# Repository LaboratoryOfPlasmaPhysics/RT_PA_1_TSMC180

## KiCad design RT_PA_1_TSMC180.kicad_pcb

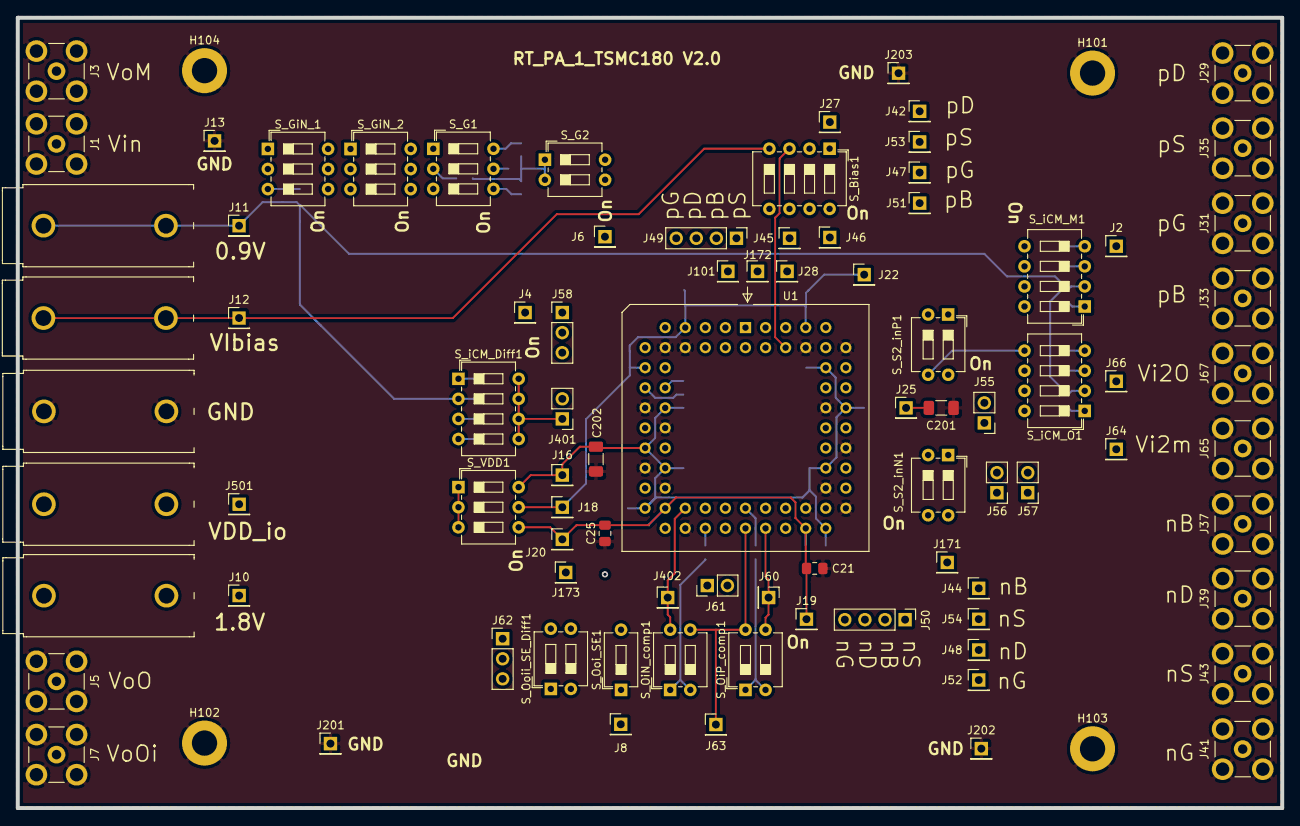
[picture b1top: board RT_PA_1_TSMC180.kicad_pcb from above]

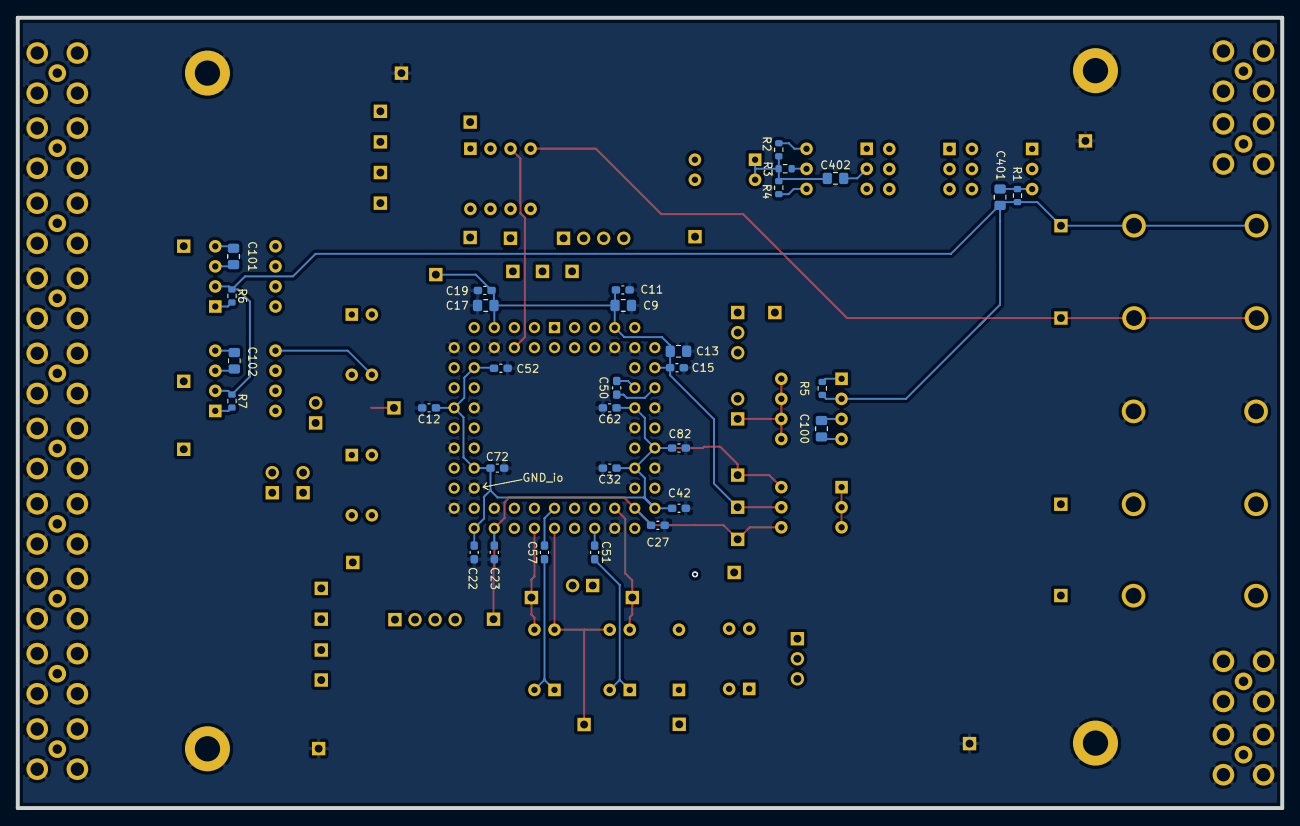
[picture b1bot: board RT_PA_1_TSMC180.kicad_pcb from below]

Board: 4 copper layers, 160.0 x 100.0 mm, 122 parts (31 on the bottom side), 57 nets.

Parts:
C9, C13, C17, C21, C25, C100, C101, C102: 1u; C_0805_2012Metric_Pad1.18x1.45mm_HandSolder
C11, C12, C15, C19, C22, C23, C27, C32, C42, C52, C62, C72, C82: 10n; C_0603_1608Metric_Pad1.08x0.95mm_HandSolder
C50, C51, C57: 1n; C_0603_1608Metric_Pad1.08x0.95mm_HandSolder
C201, C202: 10uF; C_1206_3216Metric_Pad1.33x1.80mm_HandSolder
C401, C402: NC; C_0805_2012Metric_Pad1.18x1.45mm_HandSolder
H101, H102, H103, H104: MountingHole_Pad; MountingHole_3.2mm_M3_ISO7380_Pad
J1, J3, J5, J7, J29, J31, J33, J35, J37, J39, J41, J43, J65, J67: Conn_Coaxial; SMB_Jack_Vertical
J2, J4, J6, J8, J10, J11, J12, J13, J16, J18, J19, J20, J22, J25, J27, J28, J42, J44, J45, J46, J47, J48, J51, J52, J53, J54, J60, J63, J64, J66, J101, J171, J172, J173, J201, J202, J203, J402, J501: Conn_01x01; PinHeader_1x01_P2.54mm_Vertical
J9, J14, J15, J204: Conn_01x01_Female; Banana_test_point_4mm
J49, J50: Conn_01x04; PinHeader_1x04_P2.54mm_Vertical
J55, J56, J57, J61, J401: Conn_01x02; PinHeader_1x02_P2.54mm_Vertical
J58, J62: Conn_01x03; PinHeader_1x03_P2.54mm_Vertical
J_VDD_io501: Conn_01x01_Female; Banana_test_point_4mm
R1: 50; R_0603_1608Metric
R2: 5k; R_0603_1608Metric
R3, R5, R6, R7: 50k; R_0603_1608Metric
R4: 20k; R_0603_1608Metric
S_Bias1: SW_DIP_x04; SW_DIP_SPSTx04_Slide_6.7x11.72mm_W7.62mm_P2.54mm_LowProfile
S_G1: SW_DIP_x03; SW_DIP_SPSTx03_Slide_6.7x9.18mm_W7.62mm_P2.54mm_LowProfile
S_G2: SW_DIP_x02; SW_DIP_SPSTx02_Slide_6.7x6.64mm_W7.62mm_P2.54mm_LowProfile
S_GiN_1, S_GiN_2: SW_DIP_x03; SW_DIP_SPSTx03_Slide_6.7x9.18mm_W7.62mm_P2.54mm_LowProfile
S_OiN_comp1: SW_DIP_x02; SW_DIP_SPSTx02_Slide_6.7x6.64mm_W7.62mm_P2.54mm_LowProfile
S_OiP_comp1: SW_DIP_x02; SW_DIP_SPSTx02_Slide_6.7x6.64mm_W7.62mm_P2.54mm_LowProfile
S_Ooi_SE1: SW_DIP_x01; SW_DIP_SPSTx01_Slide_6.7x4.1mm_W7.62mm_P2.54mm_LowProfile
S_Ooii_SE_Diff1: SW_DIP_x02; SW_DIP_SPSTx02_Slide_6.7x6.64mm_W7.62mm_P2.54mm_LowProfile
S_S2_inN1, S_S2_inP1: SW_DIP_x02; SW_DIP_SPSTx02_Slide_6.7x6.64mm_W7.62mm_P2.54mm_LowProfile
S_VDD1: SW_DIP_x03; SW_DIP_SPSTx03_Slide_6.7x9.18mm_W7.62mm_P2.54mm_LowProfile
S_iCM_Diff1: SW_DIP_x04; SW_DIP_SPSTx04_Slide_6.7x11.72mm_W7.62mm_P2.54mm_LowProfile
S_iCM_M1: SW_DIP_x04; SW_DIP_SPSTx04_Slide_6.7x11.72mm_W7.62mm_P2.54mm_LowProfile
S_iCM_O1: SW_DIP_x04; SW_DIP_SPSTx04_Slide_6.7x11.72mm_W7.62mm_P2.54mm_LowProfile
U1: PART1p68; PLCC-68_THT-Socket

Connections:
/0V9_g: C401.2, J11.1, J14.1, R1.2, R5.2, R6.2, R7.2, S_iCM_Diff1.2, S_iCM_M1.2, S_iCM_O1.2
/1V8_g: J9.1, J10.1, S_VDD1.1, S_VDD1.2, S_VDD1.3
/TCc1: C57.2, J61.2, U1.36
/TCc2: C51.2, J61.1, U1.31
/T_Cc: C50.2, J58.3, U1.14
/VDD_M: C9.1, C11.1, C13.1, C15.1, C17.1, C19.1, J18.1, J22.1, S_VDD1.5, U1.7, U1.12, U1.63
/VDD_O: C21.1, C23.1, C25.1, C27.1, J19.1, J20.1, S_VDD1.4, U1.28, U1.41
/VDD_diff: C12.1, C22.1, C32.1, C42.1, C52.1, C62.1, C72.1, C82.1, C201.1, C202.1, J16.1, J25.1, S_VDD1.6, U1.17, U1.20, U1.23, U1.26, U1.43, U1.49, U1.54, U1.59
/VDD_io: J501.1, J_VDD_io501.1, U1.46
/VIbias: J12.1, J15.1, J27.1, S_Bias1.1, S_Bias1.2, S_Bias1.3, S_Bias1.4, U1.66
/VM_M: J172.1, U1.2
/VM_O: J173.1, U1.24
/VM_diff: J171.1, U1.48
/Vbi: J63.1, S_Bias1.5, S_OiN_comp1.3, S_OiP_comp1.4, S_Ooi_SE1.2, U1.35
/VbiasDiff: J28.1, S_Bias1.7, U1.67
/VbiasM: J45.1, S_Bias1.6, U1.65
/VbiasO: J46.1, S_Bias1.8, U1.68
/Vi1O: J57.1, S_GiN_1.4, S_GiN_2.3, S_S2_inN1.3, U1.51
/Vi1d: J401.1, S_iCM_Diff1.5, S_iCM_Diff1.6, S_iCM_Diff1.7, S_iCM_Diff1.8, U1.21
/Vi1m: J56.1, S_GiN_1.5, S_GiN_2.2, S_S2_inN1.4, U1.53
/Vi2O: J57.2, J66.1, J67.1, S_S2_inP1.3, S_iCM_O1.5, S_iCM_O1.6, S_iCM_O1.7, S_iCM_O1.8, U1.56
/Vi2d: J401.2, S_GiN_1.6, S_GiN_2.1, U1.18
/Vi2m: J56.2, J64.1, J65.1, S_S2_inP1.4, S_iCM_M1.5, S_iCM_M1.6, S_iCM_M1.7, S_iCM_M1.8, U1.58
/Vin: C100.2, C101.2, C102.2, J1.1, J2.1, S_iCM_Diff1.4, S_iCM_M1.4, S_iCM_O1.4
/Vo1O: J60.1, S_OiP_comp1.3, U1.37
/Vo1d: J55.1, S_S2_inN1.1, S_S2_inN1.2, U1.52
/Vo1m: J101.1, U1.1
/Vo2O: J402.1, S_OiN_comp1.4, U1.30
/Vo2d: J55.2, S_S2_inP1.1, S_S2_inP1.2, U1.57
/Vo2m: C50.1, J58.2, U1.15
/VoM: J3.1, J4.1, J58.1, S_G2.4, U1.13
/VoO: J5.1, J6.1, J62.1, S_G2.3, S_Ooii_SE_Diff1.4, U1.32
/VoOi: J7.1, J8.1, J62.2, S_Ooi_SE1.1, S_Ooii_SE_Diff1.3, U1.34
/VoOii: J62.3, S_Ooii_SE_Diff1.1, S_Ooii_SE_Diff1.2, U1.33
/nB: J37.1, J44.1, J50.2, U1.45
/nD: J39.1, J48.1, J50.3, U1.40
/nG: J41.1, J50.4, J52.1, U1.39
/nS: J43.1, J50.1, J54.1, U1.38
/pB: J33.1, J49.2, J51.1, U1.4
/pD: J29.1, J42.1, J49.3, U1.6
/pG: J31.1, J47.1, J49.4, U1.5
/pS: J35.1, J49.1, J53.1, U1.3
GND: C9.2, C11.2, C12.2, C13.2, C15.2, C17.2, C19.2, C21.2, C22.2, C23.2, C25.2, C27.2, C32.2, C42.2, C52.2, C62.2, C72.2, C82.2, C201.2, C202.2, H101.1, H102.1, H103.1, H104.1, J1.2, J3.2, J5.2, J7.2, J13.1, J29.2, J31.2, J33.2, J35.2, J37.2, J39.2, J41.2, J43.2, J65.2, J67.2, J201.1, J202.1, J203.1, J204.1, U1.8, U1.11, U1.16, U1.19, U1.22, U1.25, U1.29, U1.42, U1.44, U1.47, U1.50, U1.55, U1.60, U1.64
unnamed: C51.1, S_OiN_comp1.1, S_OiN_comp1.2
unnamed: C57.1, S_OiP_comp1.1, S_OiP_comp1.2
unnamed: C100.1, S_iCM_Diff1.3
unnamed: C101.1, S_iCM_M1.3
unnamed: C102.1, S_iCM_O1.3
unnamed: C401.1, R1.1, S_GiN_1.1, S_GiN_1.2, S_GiN_1.3
unnamed: C402.1, R2.1, R3.2, R4.2, S_G2.1, S_G2.2
unnamed: C402.2, S_G1.1, S_G1.2, S_G1.3, S_GiN_2.4, S_GiN_2.5, S_GiN_2.6
unnamed: R2.2, S_G1.6
unnamed: R3.1, S_G1.5
unnamed: R4.1, S_G1.4
unnamed: R5.1, S_iCM_Diff1.1
unnamed: R6.1, S_iCM_M1.1
unnamed: R7.1, S_iCM_O1.1

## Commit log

2021-06-03 Import project from Fatima's archive
2021-06-09 Major changes in almost all project sheets
2021-06-17 Major changes in almost all project sheets-2
2021-06-20 Adds missing Bias schematic, changes few footprints and started components grouping in PCB
2021-06-22 Simplified VDD schematic nets
2021-06-22 Adds some missing connections and layout WIP
2021-06-23 Banana footprint change, added 3D models and PCB still WIP
2021-06-23 PCB layout complete, ready for review.
2021-07-01 Some modifications on schematic and Layout to be optimised!
2021-07-06 PCB ready for production
2021-07-06 Some cleanup and reversed On marker for switchs
2021-07-06 Adds some legned and one testpoint for VDD_io
2021-09-09 Fix ASIC footprint pin swap
2021-09-09 PCB updated ready for review
